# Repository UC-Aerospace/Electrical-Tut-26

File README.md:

# 2026 Avionics tutorial example boards!!
Here's where you'll find basic examples of a flight computer board using the RP2350 microcontroller. 

We have two different example sizes.  
  
(50mm x 50mm) This shows it's possible to design a 2-layer 50mm x 50mm board to fit the minimum rocket tube diameter of 50mm. Made by Grayson. This is the one we have ordered and will be avalible to pass around.  
  
~~(66mm x 66mm) This 2-layer example board is slightly bigger but small enough to fit in an L2 rocket. Made by Kaden.~~  
Unfortunatly this board has some issues at the moment, we might look into fixing it. Left for now as it shows a different general approach.

> [!NOTE]
> While making a 2-layer 50mm x 50mm board is possible, routing something this small can be quite a puzzle especially to do nicely. If you do target 50x50 we would reccomend a 4-layer board. Otherwise, we'd suggest something either 66x66mm or 88x88mm.

> [!CAUTION]
> We are not experts and are still all learning a lot ourselves. As such some of these designs may be suboptimal, don't take them as best practice. If you see an issue with any of the boards, or even just think you do, feel free to create an issue so we can all learn.

## Templates

These are barebones files to use as a starting point, and very simply include a board outline with holes that will match with our sleds, the RP2350 footprint and the Sense module footprint. Avalible in 50x50, 66x66 and 88x88 to modify as you wish.

## Resources / Datasheets
**_Please look_** at the datasheets for any major components you plan to use, e.g. (Voltage regulator, RP2350, Flash chip, Screen, LEDs, USB-C connector, etc..) They provide the information necessary to integrate them with your project and if any extra components are needed to work correctly.

The Raspberry Pi Foundation has provided a massive amount of technical information for the RP2350 microcontroller we use, so I'd suggest reviewing their datasheets to help build your boards!

[RP2350 Datasheet](https://datasheets.raspberrypi.com/rp2350/rp2350-datasheet.pdf)  
[RP2350 Hardware design examples](https://datasheets.raspberrypi.com/rp2350/hardware-design-with-rp2350.pdf)  
[Raspberry Pi Pico 2 datasheet](https://datasheets.raspberrypi.com/pico/pico-2-datasheet.pdf)
  
Also take a look at the sensor package used which we have got assembled for you:
[MicroSense](https://github.com/UC-Aerospace/Sense)

If you have any questions about the example board, then come talk to me!  
Happy making! :3

^ Demo flight computer, we will have a few to pass around.

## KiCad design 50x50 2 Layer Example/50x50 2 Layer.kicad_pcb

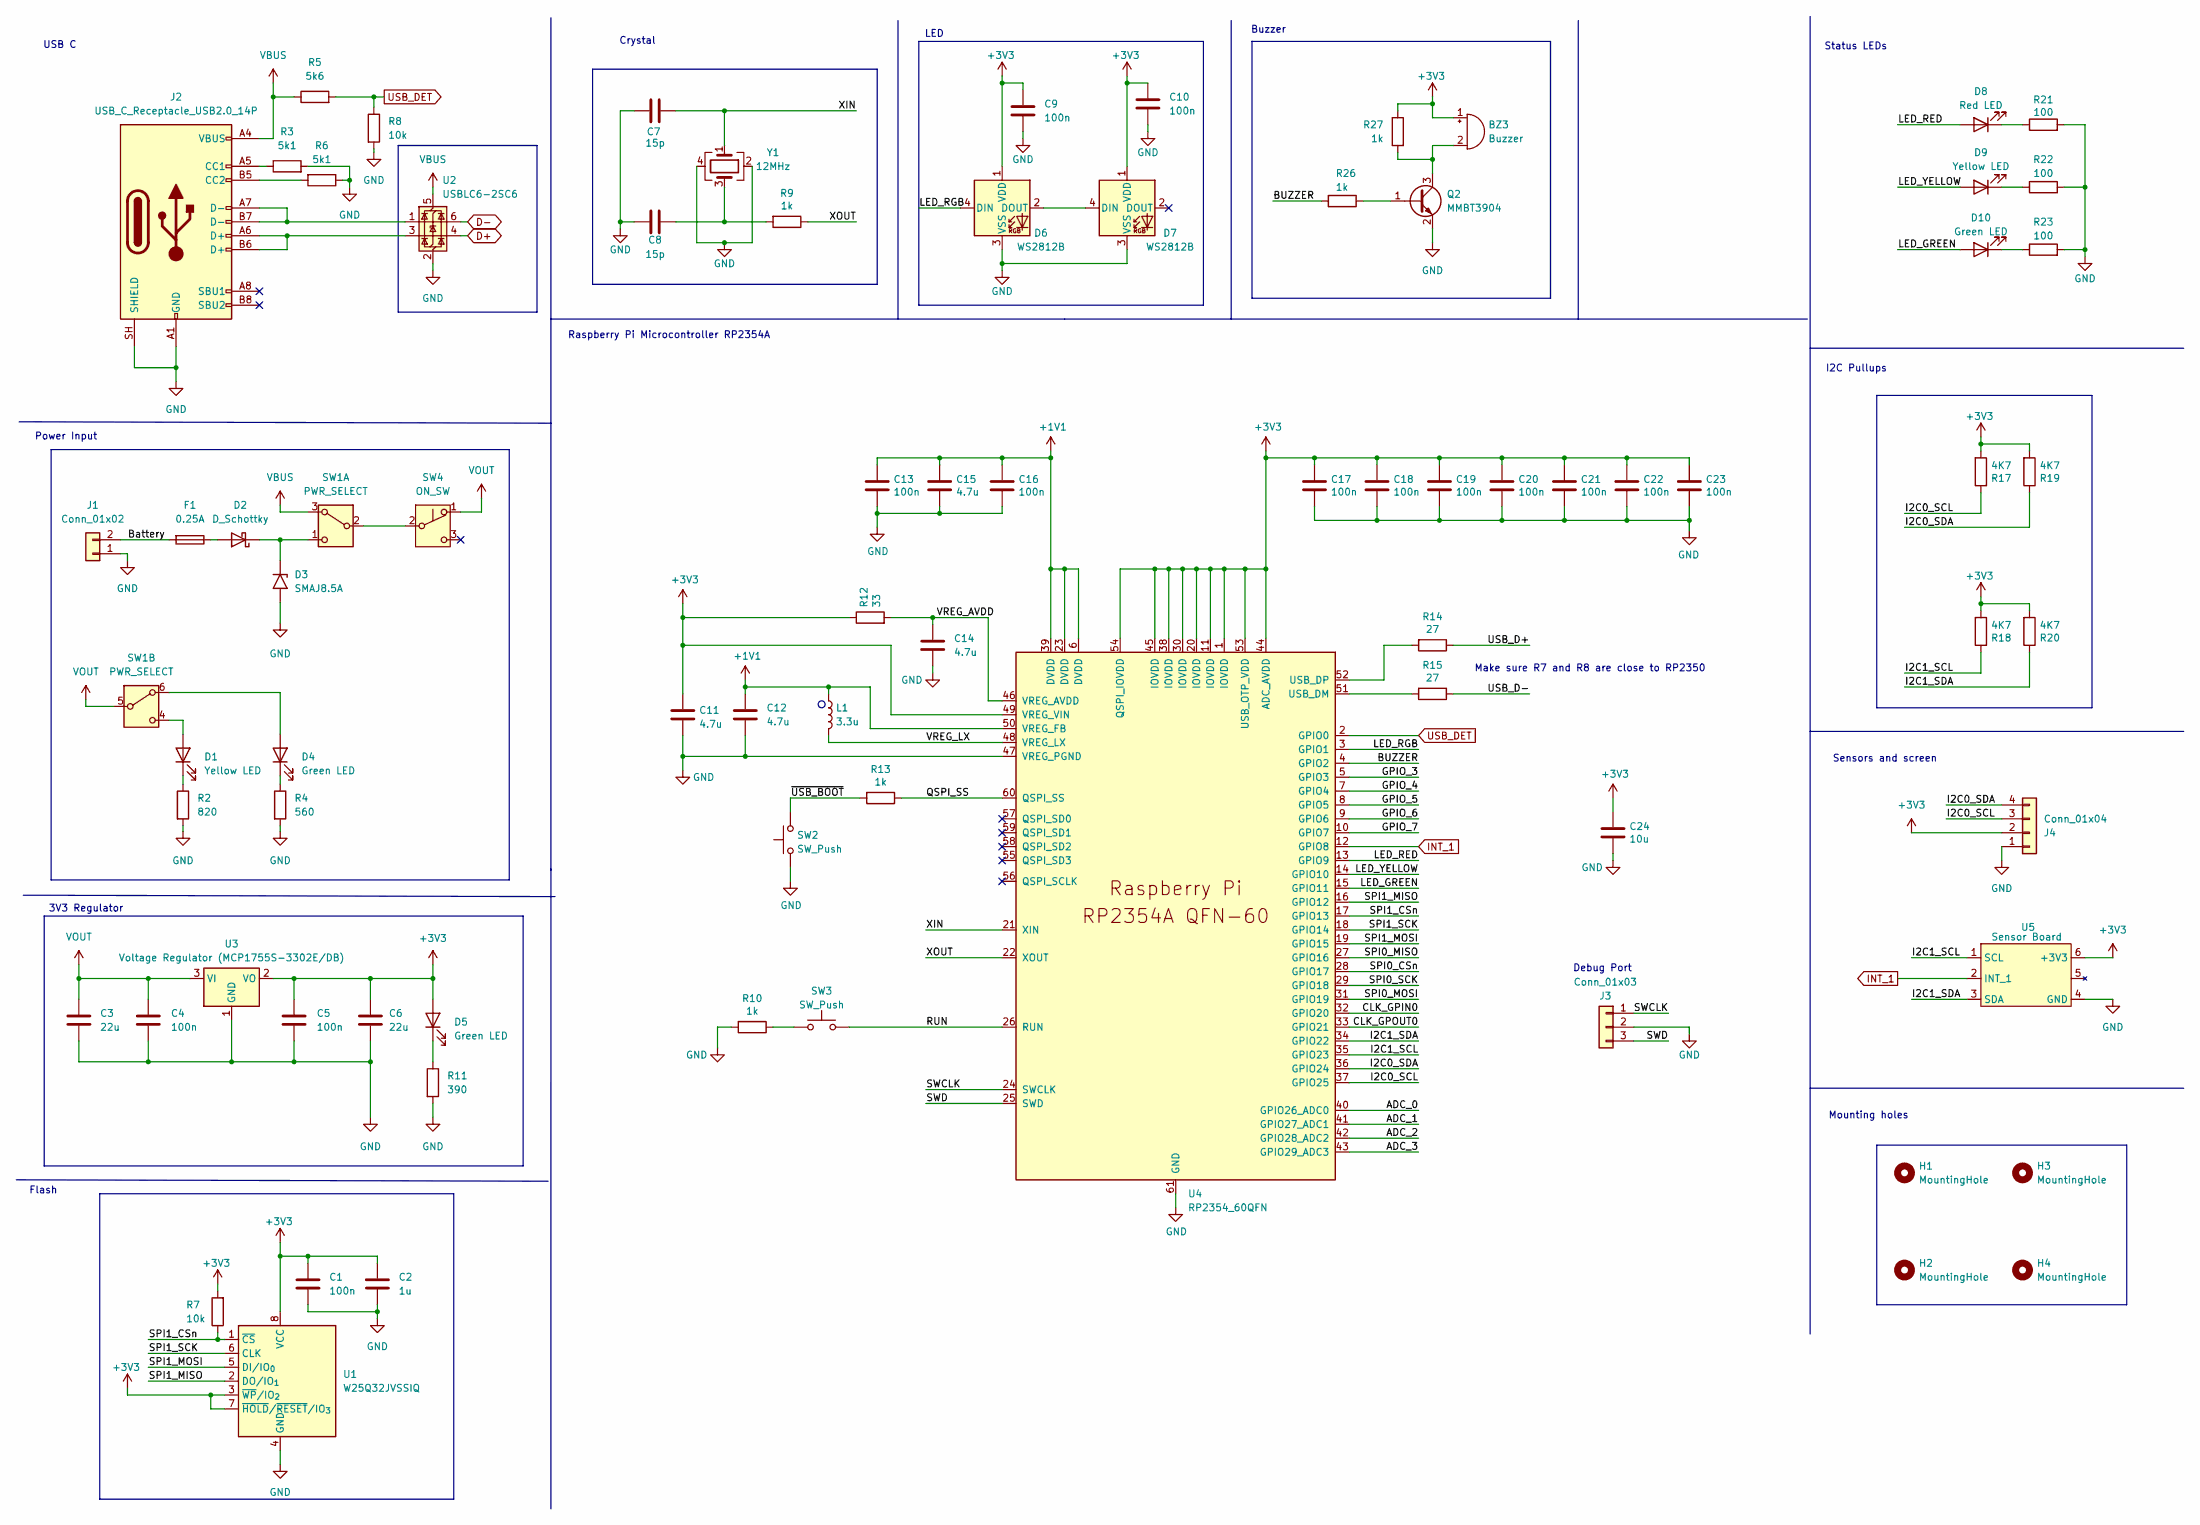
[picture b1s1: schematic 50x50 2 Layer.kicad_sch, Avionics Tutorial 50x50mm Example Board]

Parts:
BZ3: Buzzer; Buzzer_Murata_PKMCS0909E
C1, C4, C5, C9, C10: 100n; C_0603_1608Metric_Pad1.08x0.95mm_HandSolder; MPN CL21B104KCFNNNE; LCSC Part Number C28233
C2: 1u; C_0603_1608Metric_Pad1.08x0.95mm_HandSolder
C3, C6: 22u; C_0805_2012Metric; MPN CL21C200JBANNNC; LCSC Part Number C15850
C7, C8: 15p; C_0603_1608Metric_Pad1.08x0.95mm_HandSolder; MPN 0603N270J500CT; LCSC Part Number C1798
C11, C12, C14, C15: 4.7u; C_0603_1608Metric_Pad1.08x0.95mm_HandSolder
C13, C16, C17, C18, C19, C20, C21, C22, C23: 100n; C_0603_1608Metric_Pad1.08x0.95mm_HandSolder
C24: 10u; C_0805_2012Metric
D1: Yellow LED; LED_0805_2012Metric; MPN ORH-R36A; LCSC Part Number C205445
D2: D_Schottky; D_SMA; MPN SS34; LCSC Part Number C2909963
D3: SMAJ8.5A; D_SMA
D4: Green LED; LED_0805_2012Metric; MPN ORH-R36A; LCSC Part Number C205445
D5: Green LED; LED_0805_2012Metric; MPN NCD0603C1; LCSC Part Number C84264
D6, D7: WS2812B; LED_WS2812B_PLCC4_5.0x5.0mm_P3.2mm
D8: Red LED; LED_0805_2012Metric; MPN 16-213UYC/S530-A2/TR8; LCSC Part Number C136118
D9: Yellow LED; LED_0805_2012Metric; MPN 16-213SYGC/S530-E3/TR8; LCSC Part Number C264408
D10: Green LED; LED_0805_2012Metric; MPN 16-213SURC/S530-A4/TR8; LCSC Part Number C74339
F1: 0.25A; Fuse_0603_1608Metric; MPN 0467.250NRHF; LCSC Part Number C151137
H1, H2, H3, H4: MountingHole; MountingHole_3.2mm_M3
J1: Conn_01x02; JST_XH_B2B-XH-A_1x02_P2.50mm_Vertical; MPN B2B-XH-A(LF)(SN); LCSC Part Number C158012
J2: USB_C_Receptacle_USB2.0_14P; USB_C_Receptacle_GCT_USB4085; MPN GT-USB-7010ASV; LCSC Part Number C2988369
J3: Conn_01x03; PinSocket_1x03_P2.54mm_Vertical; MPN 2.54-1*3P; LCSC Part Number C146243
J4: Conn_01x04; PinSocket_1x04_P2.54mm_Vertical; MPN 2.54-1*4; LCSC Part Number C5116483
L1: 3.3u; IND-SMD_L2.0-W1.6_AOTA-B201610S3R3-101-T
Q2: MMBT3904; SOT-23
R2: 820; C_0603_1608Metric_Pad1.08x0.95mm_HandSolder; MPN RC0805FR-07470RL; LCSC Part Number C114564
R3, R6: 5k1; R_0603_1608Metric_Pad0.98x0.95mm_HandSolder; MPN 0805W8F5101T5E; LCSC Part Number C27834
R4: 560; C_0603_1608Metric_Pad1.08x0.95mm_HandSolder; MPN RC0805FR-07470RL; LCSC Part Number C114564
R5: 5k6; C_0603_1608Metric_Pad1.08x0.95mm_HandSolder; MPN 0805W8F5601T5E; LCSC Part Number C4382
R7: 10k; R_0603_1608Metric_Pad0.98x0.95mm_HandSolder
R8: 10k; R_0603_1608Metric_Pad0.98x0.95mm_HandSolder; MPN 0805W8F1002T5E; LCSC Part Number C17414
R9: 1k; R_0603_1608Metric_Pad0.98x0.95mm_HandSolder; MPN RC0805FR-074K7L; LCSC Part Number C17513
R10, R13: 1k; R_0603_1608Metric_Pad0.98x0.95mm_HandSolder
R11: 390; C_0603_1608Metric_Pad1.08x0.95mm_HandSolder; MPN RC0805JR-07360RL; LCSC Part Number C137444
R12: 33; R_0402_1005Metric
R14, R15: 27; R_0603_1608Metric_Pad0.98x0.95mm_HandSolder
R17, R18, R19, R20: 4K7; C_0603_1608Metric_Pad1.08x0.95mm_HandSolder; MPN RC0805FR-074K7L; LCSC Part Number C60816
R21, R22, R23: 100; C_0603_1608Metric_Pad1.08x0.95mm_HandSolder; MPN RC0805JR-07130RL; LCSC Part Number C137474
R26, R27: 1k; R_0603_1608Metric_Pad0.98x0.95mm_HandSolder; MPN RC0805FR-074K7L
SW1: PWR_SELECT; SW-TH_KH-SS22D07-VG4H
SW2, SW3: SW_Push; SW_SPST_TS-1088-xR020
SW4: ON_SW; SW-TH_3P-L8.6-W4.5-P2.60
U1: W25Q32JVSSIQ; SOIC-8_5.3x5.3mm_P1.27mm
U2: USBLC6-2SC6; SOT-23-6
U3: Voltage Regulator (MCP1755S-3302E/DB); SOT-23-3
U4: RP2354_60QFN; QFN-60-1EP_7x7mm_P0.4mm_EP3.4x3.4mm_ThermalVias
U5: Sensor Board; UCA_Sense
Y1: 12MHz; Crystal_SMD_3225-4Pin_3.2x2.5mm_HandSoldering; MPN ABM8-272-T3; LCSC Part Number C20625731

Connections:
+1V1: C12.1, C13.1, C15.1, C16.1, L1.1, U4.6 (DVDD), U4.23 (DVDD), U4.39 (DVDD), U4.50 (VREG_FB)
+3V3: BZ3.1 (+), C1.1, C2.1, C5.1, C6.1, C9.1, C10.1, C11.1, C17.1, C18.1, C19.1, C20.1, C21.1, C22.1, C23.1, C24.1, D5.2 (A), D6.1 (VDD), D7.1 (VDD), J4.2, R7.2, R12.1, R17.2, R18.2, R19.2, R20.2, R27.1, U1.3 (~WP/IO_{2}), U1.7 (~HOLD/~RESET/IO_{3}), U1.8 (VCC), U3.2 (VO), U4.1 (IOVDD), U4.11 (IOVDD), U4.20 (IOVDD), U4.30 (IOVDD), U4.38 (IOVDD), U4.44 (ADC_AVDD), U4.45 (IOVDD), U4.49 (VREG_VIN), U4.53 (USB_OTP_VDD), U4.54 (QSPI_IOVDD), U5.6 (+3V3)
/ADC_0: U4.40 (GPIO26_ADC0)
/ADC_1: U4.41 (GPIO27_ADC1)
/ADC_2: U4.42 (GPIO28_ADC2)
/ADC_3: U4.43 (GPIO29_ADC3)
/BUZZER: R26.2, U4.4 (GPIO2)
/Battery: F1.2, J1.2
/CLK_GPIN0: U4.32 (GPIO20)
/CLK_GPOUT0: U4.33 (GPIO21)
/GPIO_3: U4.5 (GPIO3)
/GPIO_4: U4.7 (GPIO4)
/GPIO_5: U4.8 (GPIO5)
/GPIO_6: U4.9 (GPIO6)
/GPIO_7: U4.10 (GPIO7)
/I2C0_SCL: J4.3, R17.1, U4.37 (GPIO25)
/I2C0_SDA: J4.4, R19.1, U4.36 (GPIO24)
/I2C1_SCL: R18.1, U4.35 (GPIO23), U5.1 (SCL)
/I2C1_SDA: R20.1, U4.34 (GPIO22), U5.3 (SDA)
/LED_GREEN: D10.2 (A), U4.15 (GPIO11)
/LED_RED: D8.2 (A), U4.13 (GPIO9)
/LED_RGB: D6.4 (DIN), U4.3 (GPIO1)
/LED_YELLOW: D9.2 (A), U4.14 (GPIO10)
/QSPI_SS: R13.1, U4.60 (QSPI_SS)
/RUN: SW3.2, U4.26 (RUN)
/SPI0_CSn: U4.28 (GPIO17)
/SPI0_MISO: U4.27 (GPIO16)
/SPI0_MOSI: U4.31 (GPIO19)
/SPI0_SCK: U4.29 (GPIO18)
/SPI1_CSn: R7.1, U1.1 (~CS), U4.17 (GPIO13)
/SPI1_MISO: U1.2 (DO/IO_{1}), U4.16 (GPIO12)
/SPI1_MOSI: U1.5 (DI/IO_{0}), U4.19 (GPIO15)
/SPI1_SCK: U1.6 (CLK), U4.18 (GPIO14)
/SWCLK: J3.1, U4.24 (SWCLK)
/SWD: J3.3, U4.25 (SWD)
/USB_D+: R14.1
/USB_D-: R15.1
/VREG_AVDD: C14.1, R12.2, U4.46 (VREG_AVDD)
/VREG_LX: L1.2, U4.48 (VREG_LX)
/XIN: C7.1, U4.21 (XIN), Y1.1
/XOUT: R9.1, U4.22 (XOUT)
/~USB_BOOT: R13.2, SW2.2
D+: U2.4 (I/O2)
D-: U2.6 (I/O1)
GND: C1.2, C2.2, C3.2, C4.2, C5.2, C6.2, C7.2, C8.2, C9.2, C10.2, C11.2, C12.2, C13.2, C14.2, C15.2, C16.2, C17.2, C18.2, C19.2, C20.2, C21.2, C22.2, C23.2, C24.2, D3.2 (A2), D6.3 (VSS), D7.3 (VSS), J1.1, J2.A1 (GND), J2.A12 (GND), J2.B1 (GND), J2.B12 (GND), J2.SH (SHIELD), J3.2, J4.1, Q2.2 (E), R2.2, R3.2, R4.2, R6.1, R8.2, R10.2, R11.2, R21.2, R22.2, R23.2, SW2.1, U1.4 (GND), U2.2 (GND), U3.1 (GND), U4.47 (VREG_PGND), U4.61 (GND), U5.4 (GND), Y1.2, Y1.4
INT_1: U4.12 (GPIO8), U5.2 (INT_1)
unnamed: BZ3.2 (-), Q2.3 (C), R27.2
unnamed: C8.1, R9.2, Y1.3
unnamed: D1.2 (A), SW1.4 (A)
unnamed: D1.1 (K), R2.1
unnamed: D2.2 (A), F1.1
unnamed: D2.1 (K), D3.1 (A1), SW1.1 (A)
unnamed: D4.2 (A), SW1.6 (C)
unnamed: D4.1 (K), R4.1
unnamed: D5.1 (K), R11.1
unnamed: D6.2 (DOUT), D7.4 (DIN)
unnamed: D8.1 (K), R21.1
unnamed: D9.1 (K), R22.1
unnamed: D10.1 (K), R23.1
unnamed: J2.A5 (CC1), R3.1
unnamed: J2.B5 (CC2), R6.2
unnamed: J2.A6 (D+), J2.B6 (D+), U2.3 (I/O2)
unnamed: J2.A7 (D-), J2.B7 (D-), U2.1 (I/O1)
unnamed: Q2.1 (B), R26.1
unnamed: R10.1, SW3.1
unnamed: SW1.2 (B), SW4.2 (B)
unnamed: R15.2, U4.51 (USB_DM)
unnamed: R14.2, U4.52 (USB_DP)
USB_DET: R5.2, R8.1, U4.2 (GPIO0)
VBUS: J2.A4 (VBUS), J2.A9 (VBUS), J2.B4 (VBUS), J2.B9 (VBUS), R5.1, SW1.3 (C), U2.5 (VBUS)
VOUT: C3.1, C4.1, SW1.5 (B), SW4.1 (A), U3.3 (VI)

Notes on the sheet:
Sensors and screen
Debug Port
Raspberry Pi Microcontroller RP2354A
Mounting holes
Buzzer
Crystal
Make sure R7 and R8 are close to RP2350
I2C Pullups
3V3 Regulator
Power Input
Flash
USB C
LED
Status LEDs

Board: 2 copper layers, 79 parts (0 on the bottom side), 52 nets, no tracks yet.

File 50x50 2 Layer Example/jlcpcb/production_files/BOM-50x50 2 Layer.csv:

Comment,Designator,Footprint,LCSC,Quantity
0.25A,F1,Fuse_0603_1608Metric,C151137,1
100,"R21,R22,R23",C_0603_1608Metric_Pad1.08x0.95mm_HandSolder,C22775,3
100n,"C1,C10,C13,C16,C17,C18,C19,C20,C21,C22,C23,C4,C5,C9",C_0603_1608Metric_Pad1.08x0.95mm_HandSolder,C14663,14
10k,"R7,R8",R_0603_1608Metric_Pad0.98x0.95mm_HandSolder,C25804,2
10u,C24,C_0805_2012Metric,C15850,1
12MHz,Y1,Crystal_SMD_3225-4Pin_3.2x2.5mm_HandSoldering,C20625731,1
15p,"C7,C8",C_0603_1608Metric_Pad1.08x0.95mm_HandSolder,C1644,2
1k,"R10,R13,R26,R27,R9",R_0603_1608Metric_Pad0.98x0.95mm_HandSolder,C21190,5
1u,C2,C_0603_1608Metric_Pad1.08x0.95mm_HandSolder,C15849,1
22u,"C3,C6",C_0805_2012Metric,C45783,2
27,"R14,R15",R_0603_1608Metric_Pad0.98x0.95mm_HandSolder,C25190,2
3.3u,L1,IND-SMD_L2.0-W1.6_AOTA-B201610S3R3-101-T,C42411119,1
33,R12,R_0603_1608Metric_Pad0.98x0.95mm_HandSolder,C23140,1
390,R11,C_0603_1608Metric_Pad1.08x0.95mm_HandSolder,C23151,1
4.7u,"C11,C12,C14,C15",C_0603_1608Metric_Pad1.08x0.95mm_HandSolder,C17673,4
4K7,"R17,R18,R19,R20",C_0603_1608Metric_Pad1.08x0.95mm_HandSolder,C23162,4
560,R4,C_0603_1608Metric_Pad1.08x0.95mm_HandSolder,C23204,1
5k1,"R3,R6",R_0603_1608Metric_Pad0.98x0.95mm_HandSolder,C27834,2
5k6,R5,C_0603_1608Metric_Pad1.08x0.95mm_HandSolder,C4382,1
820,R2,C_0603_1608Metric_Pad1.08x0.95mm_HandSolder,C23253,1
Buzzer,BZ3,Buzzer_Murata_PKMCS0909E,C910763,1
Conn_01x02,J1,JST_XH_B2B-XH-A_1x02_P2.50mm_Vertical,C158012,1
Conn_01x03,J3,PinSocket_1x03_P2.54mm_Vertical,C146243,1
Conn_01x04,J4,PinSocket_1x04_P2.54mm_Vertical,C5116483,1
D_Schottky,D2,D_SMA,C8678,1
Green LED,"D10,D4,D5",LED_0805_2012Metric,C2297,3
MMBT3904,Q2,SOT-23,C7420353,1
ON_SW,SW4,SW-TH_3P-L8.6-W4.5-P2.60,C2857672,1
PWR_SELECT,SW1,SW-TH_KH-SS22D07-VG4H,C5274482,1
RP2354_60QFN,U4,QFN-60-1EP_7x7mm_P0.4mm_EP3.4x3.4mm_ThermalVias,C41378174,1
Red LED,D8,LED_0805_2012Metric,C84256,1
SMAJ8.5A,D3,D_SMA,C49424014,1
SW_Push,"SW2,SW3",SW_SPST_TS-1088-xR020,C720477,2
USBLC6-2SC6,U2,SOT-23-6,C7519,1
USB_C_Receptacle_USB2.0_14P,J2,USB_C_Receptacle_GCT_USB4085,C2988369,1
Voltage Regulator (MCP1755S-3302E/DB),U3,SOT-23-3,C638611,1
W25Q32JVSSIQ,U1,SOIC-8_5.3x5.3mm_P1.27mm,C179173,1
WS2812B,"D6,D7",LED_WS2812B_PLCC4_5.0x5.0mm_P3.2mm,C965555,2
Yellow LED,"D1,D9",LED_0805_2012Metric,C2296,2
Sensor Board,U5,UCA_Sense,,1
